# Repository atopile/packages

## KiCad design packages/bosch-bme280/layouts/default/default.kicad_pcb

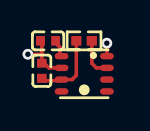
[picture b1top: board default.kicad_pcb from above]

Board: 2 copper layers, 4 parts (0 on the bottom side), 4 nets.

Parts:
C1, C2: 1F; C0402
R1: 10000Ω; R0402
U1: LGA-8_BME280_BL

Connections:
CSB: R1.2, U1.2
decoupling_caps[0]-power-hv: C1.1, U1.8
hv: C2.1, R1.1, U1.6
lv: C1.2, C2.2, U1.1, U1.5, U1.7

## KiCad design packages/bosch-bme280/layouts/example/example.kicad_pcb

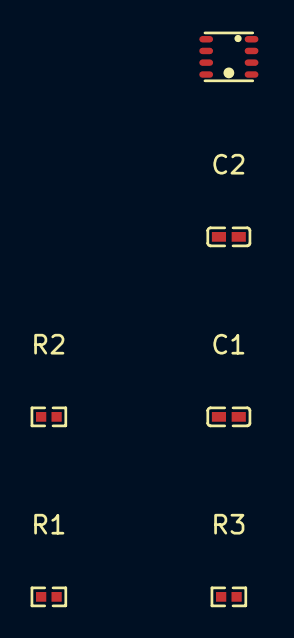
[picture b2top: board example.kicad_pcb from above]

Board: 2 copper layers, 6 parts (0 on the bottom side), 5 nets, no tracks yet.

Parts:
C1, C2: 100nF ±10% 16V X7R; C0402
R1, R2, R3: 10kΩ ±1% 62.5mW; R0402
U1: LGA-8_BME280_BL

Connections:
CSB: R3.2, U1.2
SCK: R1.1, U1.4
SDI: R2.1, U1.3
gnd: C1.2, C2.2, U1.1, U1.7
hv: C1.1, C2.1, R1.2, R2.2, R3.1, U1.6, U1.8

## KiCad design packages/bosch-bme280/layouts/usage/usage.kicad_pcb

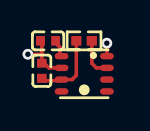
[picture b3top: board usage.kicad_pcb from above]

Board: 2 copper layers, 4 parts (0 on the bottom side), 3 nets.

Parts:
C1, C2: 1F; C0402
R1: 10000Ω; R0402
U1: LGA-8_BME280_BL

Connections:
CSB: R1.2, U1.2
hv: C1.1, C2.1, R1.1, U1.5, U1.6, U1.8
lv: C1.2, C2.2, U1.1, U1.7
